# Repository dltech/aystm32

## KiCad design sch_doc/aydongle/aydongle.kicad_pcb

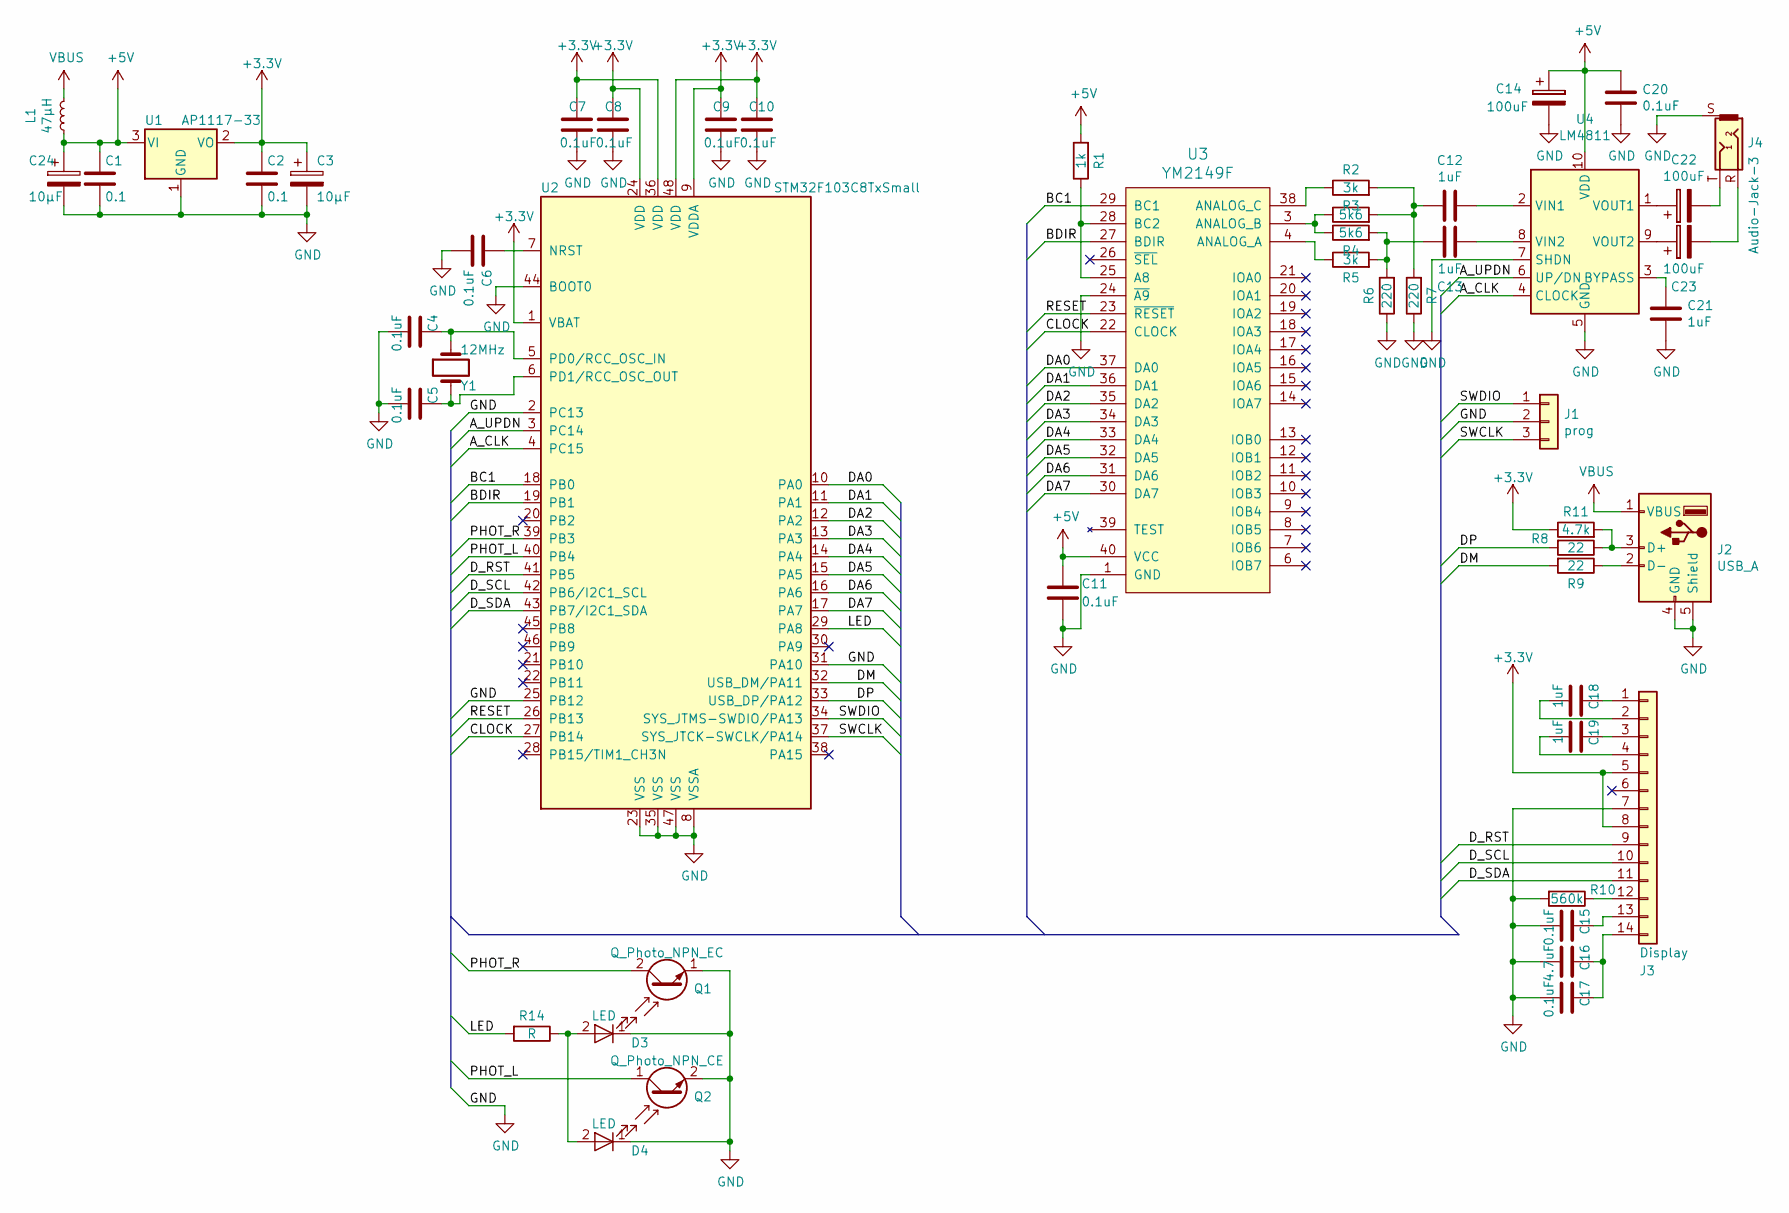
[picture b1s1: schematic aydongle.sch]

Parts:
C1, C2: 0.1; C_0603_1608Metric
C3, C24: 10µF; C_1206_3216Metric
C4, C5, C6, C7, C8, C9, C10, C11, C15, C17, C20: 0.1uF; C_0603_1608Metric
C12, C13, C18, C19, C21: 1uF; C_0805_2012Metric
C14, C22, C23: 100uF; C_1206_3216Metric
C16: 4.7uF; C_0805_2012Metric
D3, D4: LED; LED_0603_1608Metric_Castellated
J1: prog; Resonator_SMD_muRata_TPSKA-3Pin_7.9x3.8mm_HandSoldering
J2: USB_A; USB_A_CNCTech_1001-011-01101_Horizontal
J3: Display; display_14p
J4: Audio-Jack-3; phone_jack
L1: 47µH; L_1210_3225Metric
Q1: Q_Photo_NPN_EC; LED_D3.0mm_Horizontal_O1.27mm_Z2.0mm
Q2: Q_Photo_NPN_CE; LED_D3.0mm_Horizontal_O1.27mm_Z2.0mm
R1: 1k; R_0805_2012Metric
R2, R5: 3k; R_0805_2012Metric
R3, R4: 5k6; R_0805_2012Metric
R6, R7: 220; R_0805_2012Metric
R8, R9: 22; R_0805_2012Metric
R10: 560k; R_0805_2012Metric
R11: 4.7k; R_0805_2012Metric
R14: R; R_0805_2012Metric
U1: AP1117-33; SOT-223
U2: STM32F103C8TxSmall; LQFP-48_7x7mm_P0.5mm
U3: YM2149F; DIP-40_W15.24mm
U4: LM4811; VSSOP-10_3x3mm_P0.5mm
Y1: 12MHz; Crystal_SMD_0603-4Pin_6.0x3.5mm

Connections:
+3V3: C2.1, C3.1, C7.2, C8.2, C9.2, C10.2, J3.5, J3.8, R11.1, U1.2 (VO), U2.1 (VBAT), U2.9 (VDDA), U2.24 (VDD), U2.36 (VDD), U2.48 (VDD)
+5V: C1.1, C11.2, C14.1, C20.2, C24.1, L1.1, R1.2, U1.3 (VI), U3.40 (VCC), U4.10 (VDD)
/A_CLK: U2.4 (PC15), U4.4 (CLOCK)
/A_UPDN: U2.3 (PC14), U4.6 (UP/DN)
/BC1: U2.18 (PB0), U3.29 (BC1)
/BDIR: U2.19 (PB1), U3.27 (BDIR)
/CLOCK: U2.27 (PB14), U3.22 (CLOCK)
/DA0: U2.10 (PA0), U3.37 (DA0)
/DA1: U2.11 (PA1), U3.36 (DA1)
/DA2: U2.12 (PA2), U3.35 (DA2)
/DA3: U2.13 (PA3), U3.34 (DA3)
/DA4: U2.14 (PA4), U3.33 (DA4)
/DA5: U2.15 (PA5), U3.32 (DA5)
/DA6: U2.16 (PA6), U3.31 (DA6)
/DA7: U2.17 (PA7), U3.30 (DA7)
/DM: R9.2, U2.32 (USB_DM/PA11)
/DP: R8.2, U2.33 (USB_DP/PA12)
/D_RST: J3.9, U2.41 (PB5)
/D_SCL: J3.10, U2.42 (PB6/I2C1_SCL)
/D_SDA: J3.11, U2.43 (PB7/I2C1_SDA)
/LED: R14.2, U2.29 (PA8)
/PHOT_L: Q2.1 (C), U2.40 (PB4)
/PHOT_R: Q1.2 (C), U2.39 (PB3)
/RESET: U2.26 (PB13), U3.23 (~RESET~)
/SWCLK: J1.3, U2.37 (SYS_JTCK-SWCLK/PA14)
/SWDIO: J1.1, U2.34 (SYS_JTMS-SWDIO/PA13)
GND: C1.2, C2.2, C3.2, C4.1, C5.1, C6.1, C7.1, C8.1, C9.1, C10.1, C11.1, C14.2, C15.1, C16.1, C17.1, C20.1, C21.1, C24.2, D3.1 (K), D4.1 (K), J1.2, J2.4 (GND), J2.5 (Shield), J3.7, J4.S, Q1.1 (E), Q2.2 (E), R6.1, R7.1, R10.2, U1.1 (GND), U2.2 (PC13), U2.8 (VSSA), U2.23 (VSS), U2.25 (PB12), U2.31 (PA10), U2.35 (VSS), U2.44 (BOOT0), U2.47 (VSS), U3.1 (GND), U3.24 (~A9~), U4.5 (GND), U4.7 (SHDN)
unnamed: C4.2, U2.5 (PD0/RCC_OSC_IN), Y1.1
unnamed: C5.2, U2.6 (PD1/RCC_OSC_OUT), Y1.2
unnamed: C6.2, U2.7 (NRST)
unnamed: C12.1, U4.2 (VIN1)
unnamed: C12.2, R2.2, R3.2, R7.2
unnamed: C13.1, U4.8 (VIN2)
unnamed: C13.2, R4.2, R5.2, R6.2
unnamed: C15.2, J3.13
unnamed: C16.2, C17.2, J3.14
unnamed: C18.1, J3.2
unnamed: C18.2, J3.1
unnamed: C19.1, J3.4
unnamed: C19.2, J3.3
unnamed: C21.2, U4.3 (BYPASS)
unnamed: C22.1, U4.1 (VOUT1)
unnamed: C22.2, J4.T
unnamed: C23.1, U4.9 (VOUT2)
unnamed: C23.2, J4.R
unnamed: D3.2 (A), D4.2 (A), R14.1
unnamed: J2.2 (D-), R9.1
unnamed: J2.3 (D+), R8.1, R11.2
unnamed: J3.12, R10.1
unnamed: R1.1, U3.25 (A8), U3.28 (BC2)
unnamed: R2.1, U3.38 (ANALOG_C)
unnamed: R3.1, R4.1, U3.3 (ANALOG_B)
unnamed: R5.1, U3.4 (ANALOG_A)
VBUS: J2.1 (VBUS), L1.2

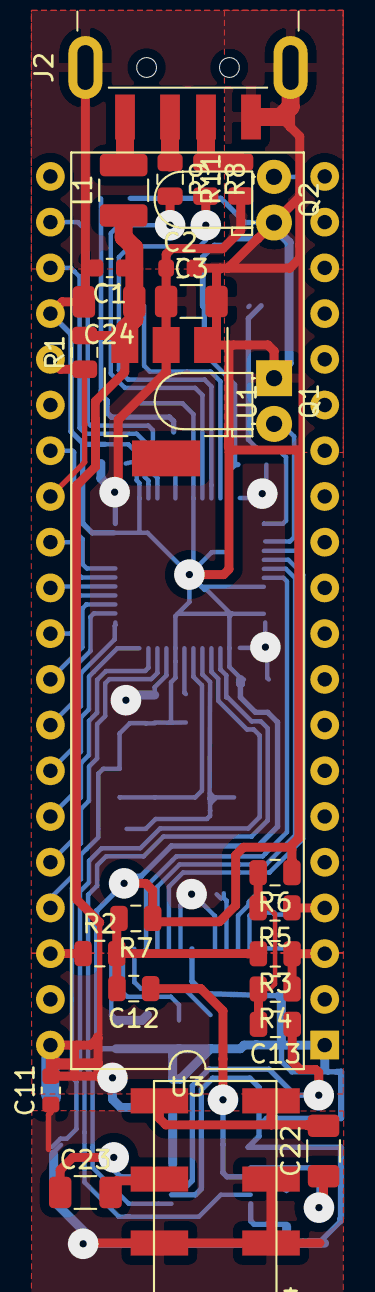
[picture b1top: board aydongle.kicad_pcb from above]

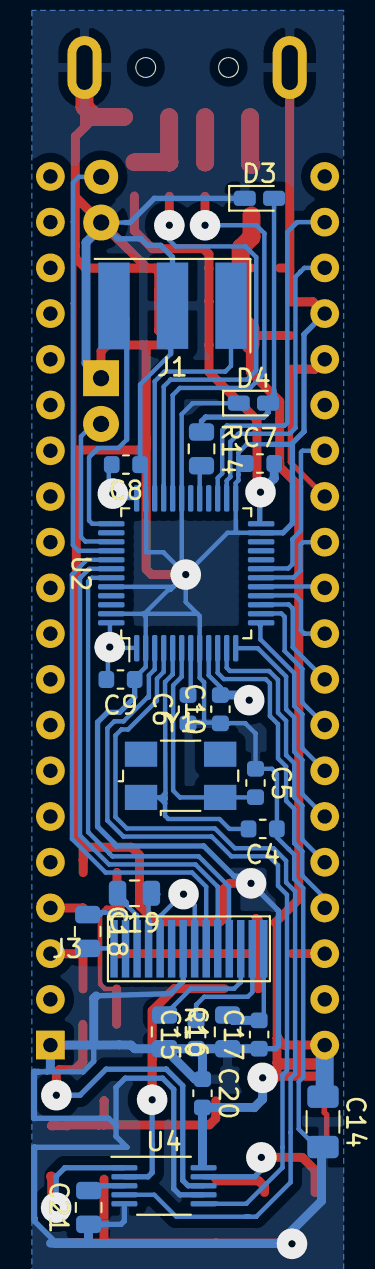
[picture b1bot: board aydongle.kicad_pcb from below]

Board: 2 copper layers, 50 parts (24 on the bottom side), 54 nets.

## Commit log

2019-11-26 сделал схему
2019-11-30 пополнил todo list
2019-11-30 доделал схему, надеюсь окончательный вариант
2019-12-04 два байта
2019-12-05 две строки
2019-12-05 ignore
2019-12-06 настройки экрана вбил
2019-12-13 еще две строчки
2019-12-13 инициализщация дисплея готова, наверно
2020-02-06 изменения
2020-05-09 собралось
2020-05-10 усилитель и ay доделал, звуков не издает
2020-05-16 работает чип и усилитель
2020-05-23 пришло время выкинуть экран
